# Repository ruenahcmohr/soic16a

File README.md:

# soicAdapter
narrow soic16 to dip adater for breadboarding room.

internet inspired narrow soic16 adapter

5pcs jlcpcb were $3.20 (because I paid with paypal)

The zip file is all the gerber files to have it made.

Hey, you dont have to populate the capacitor if you don't want to.

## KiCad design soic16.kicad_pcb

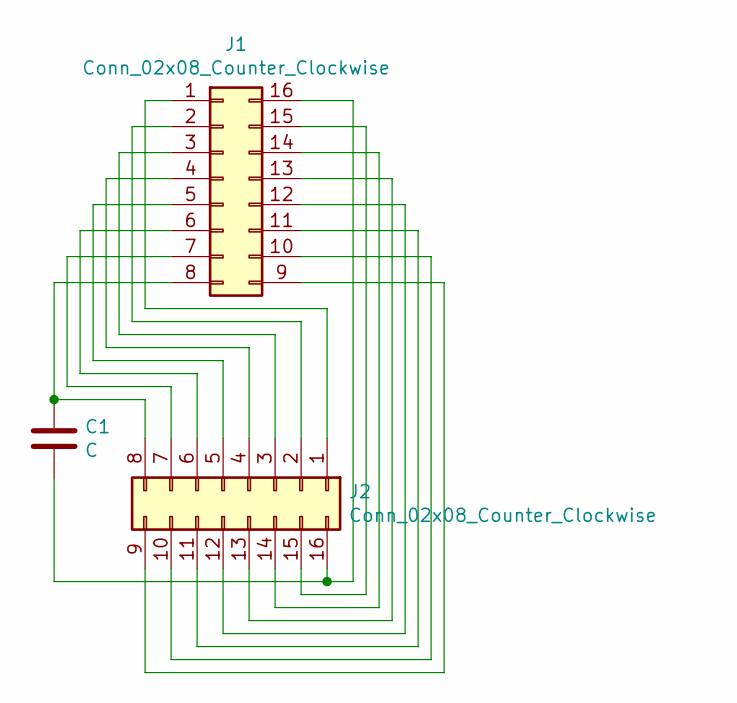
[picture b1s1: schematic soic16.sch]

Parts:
C1: C; C_0805_2012Metric_Pad1.15x1.40mm_HandSolder
J1: Conn_02x08_Counter_Clockwise; DIP-16_W7.62mm
J2: Conn_02x08_Counter_Clockwise; SOIC-16_3.9x9.9mm_P1.27mm

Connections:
unnamed: C1.1, J1.8, J2.8
unnamed: C1.2, J1.16, J2.16
unnamed: J1.1, J2.1
unnamed: J1.2, J2.2
unnamed: J1.3, J2.3
unnamed: J1.4, J2.4
unnamed: J1.5, J2.5
unnamed: J1.6, J2.6
unnamed: J1.7, J2.7
unnamed: J1.9, J2.9
unnamed: J1.10, J2.10
unnamed: J1.11, J2.11
unnamed: J1.12, J2.12
unnamed: J1.13, J2.13
unnamed: J1.14, J2.14
unnamed: J1.15, J2.15

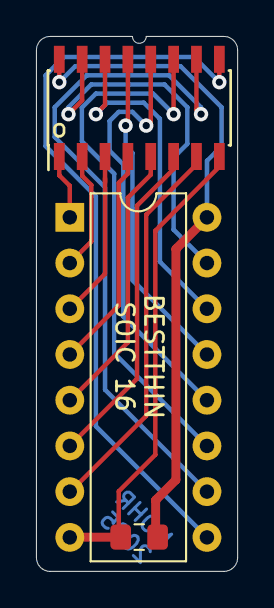
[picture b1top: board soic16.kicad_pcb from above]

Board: 2 copper layers, 11.2 x 29.7 mm, 3 parts (0 on the bottom side), 16 nets.

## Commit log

2025-02-20 adding files
2025-03-06 photo update
2025-03-06 text update
